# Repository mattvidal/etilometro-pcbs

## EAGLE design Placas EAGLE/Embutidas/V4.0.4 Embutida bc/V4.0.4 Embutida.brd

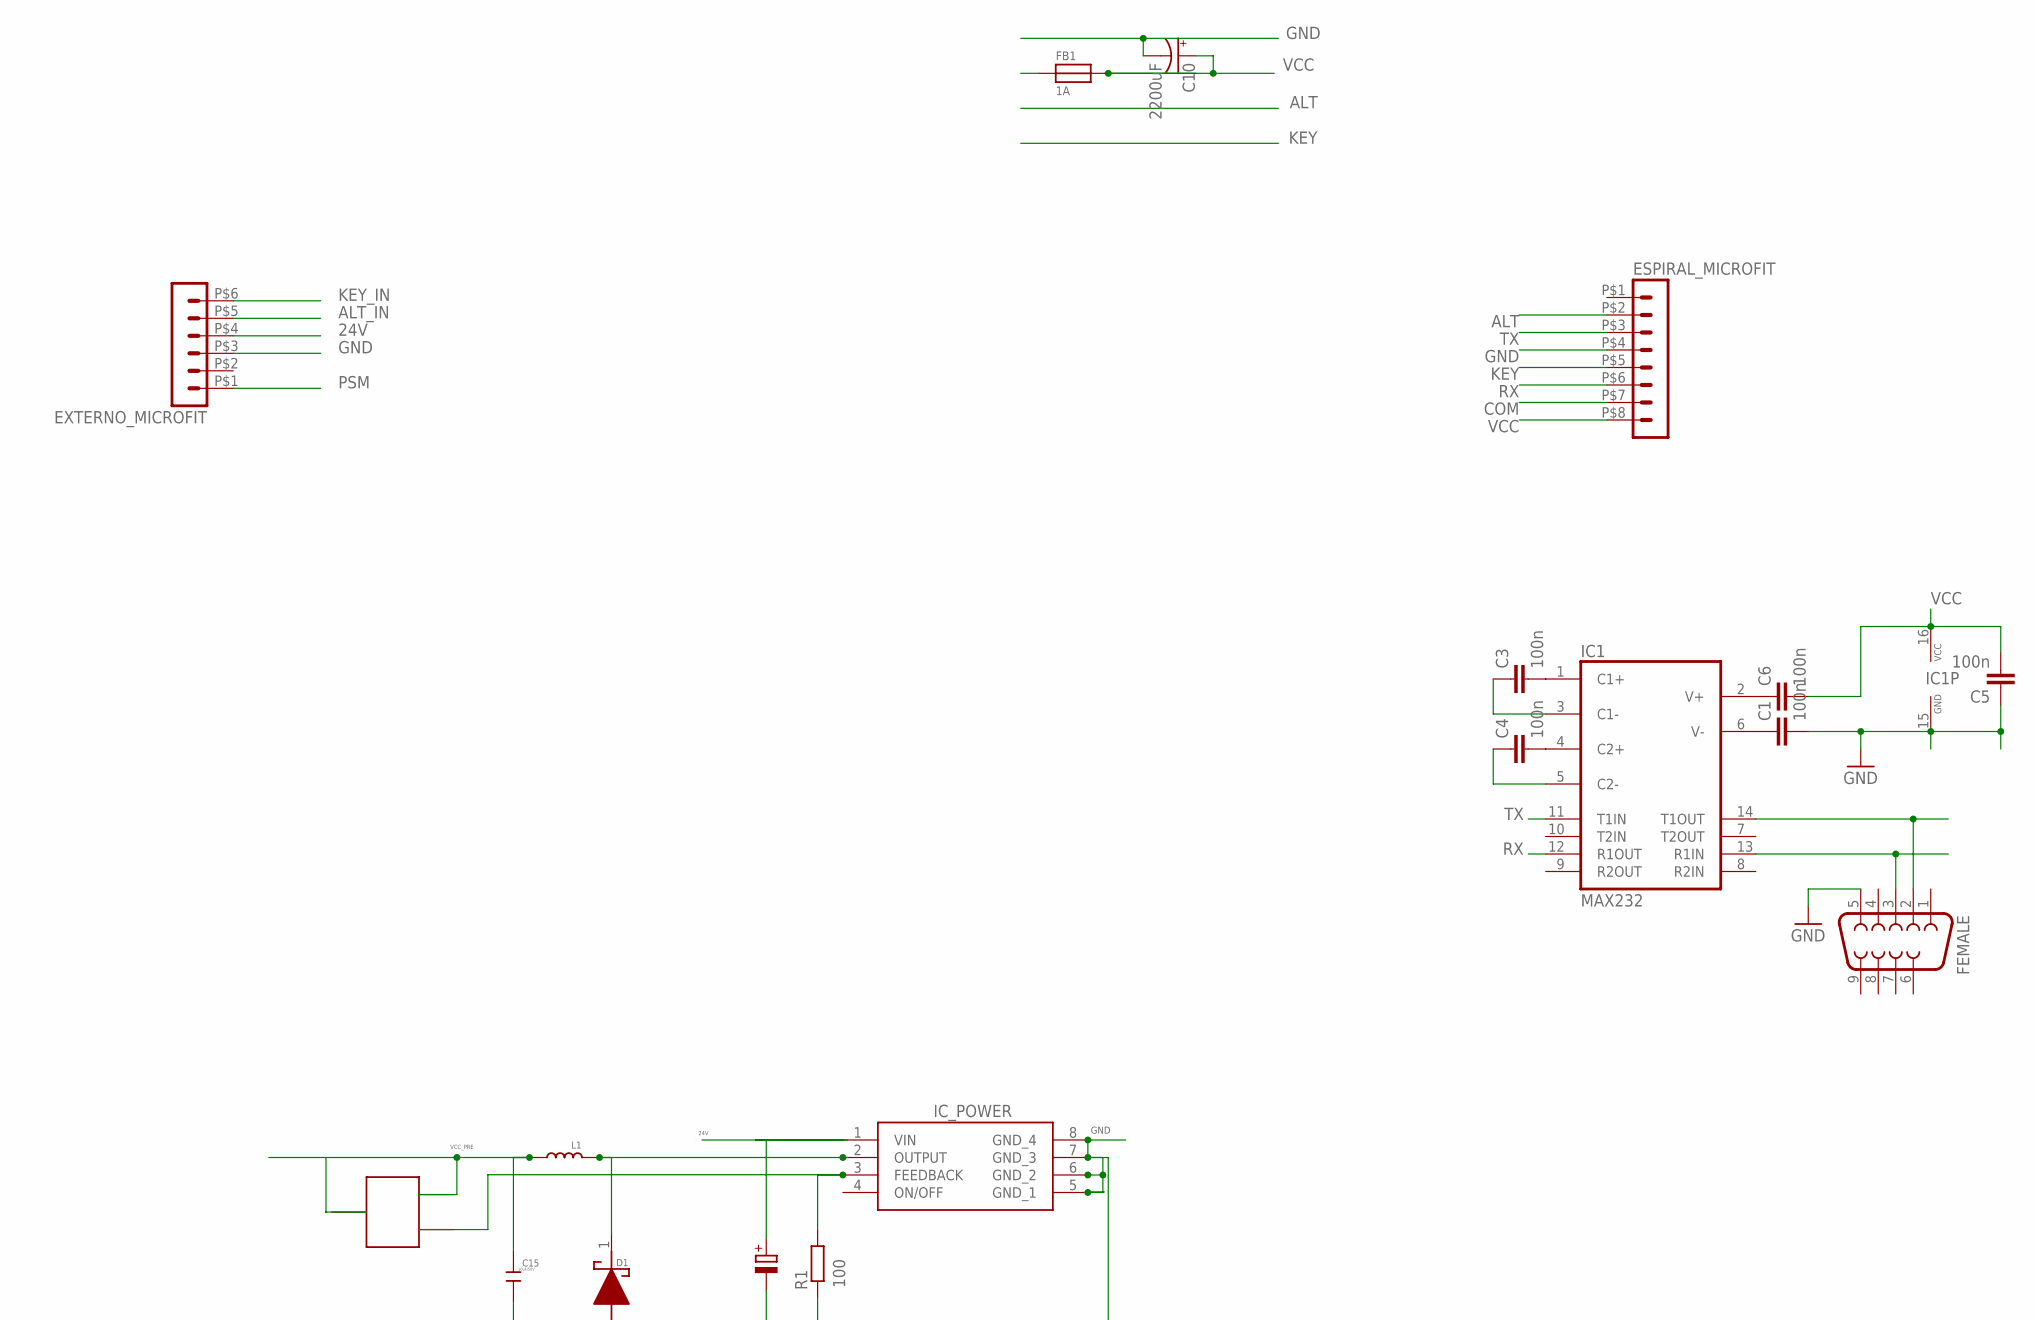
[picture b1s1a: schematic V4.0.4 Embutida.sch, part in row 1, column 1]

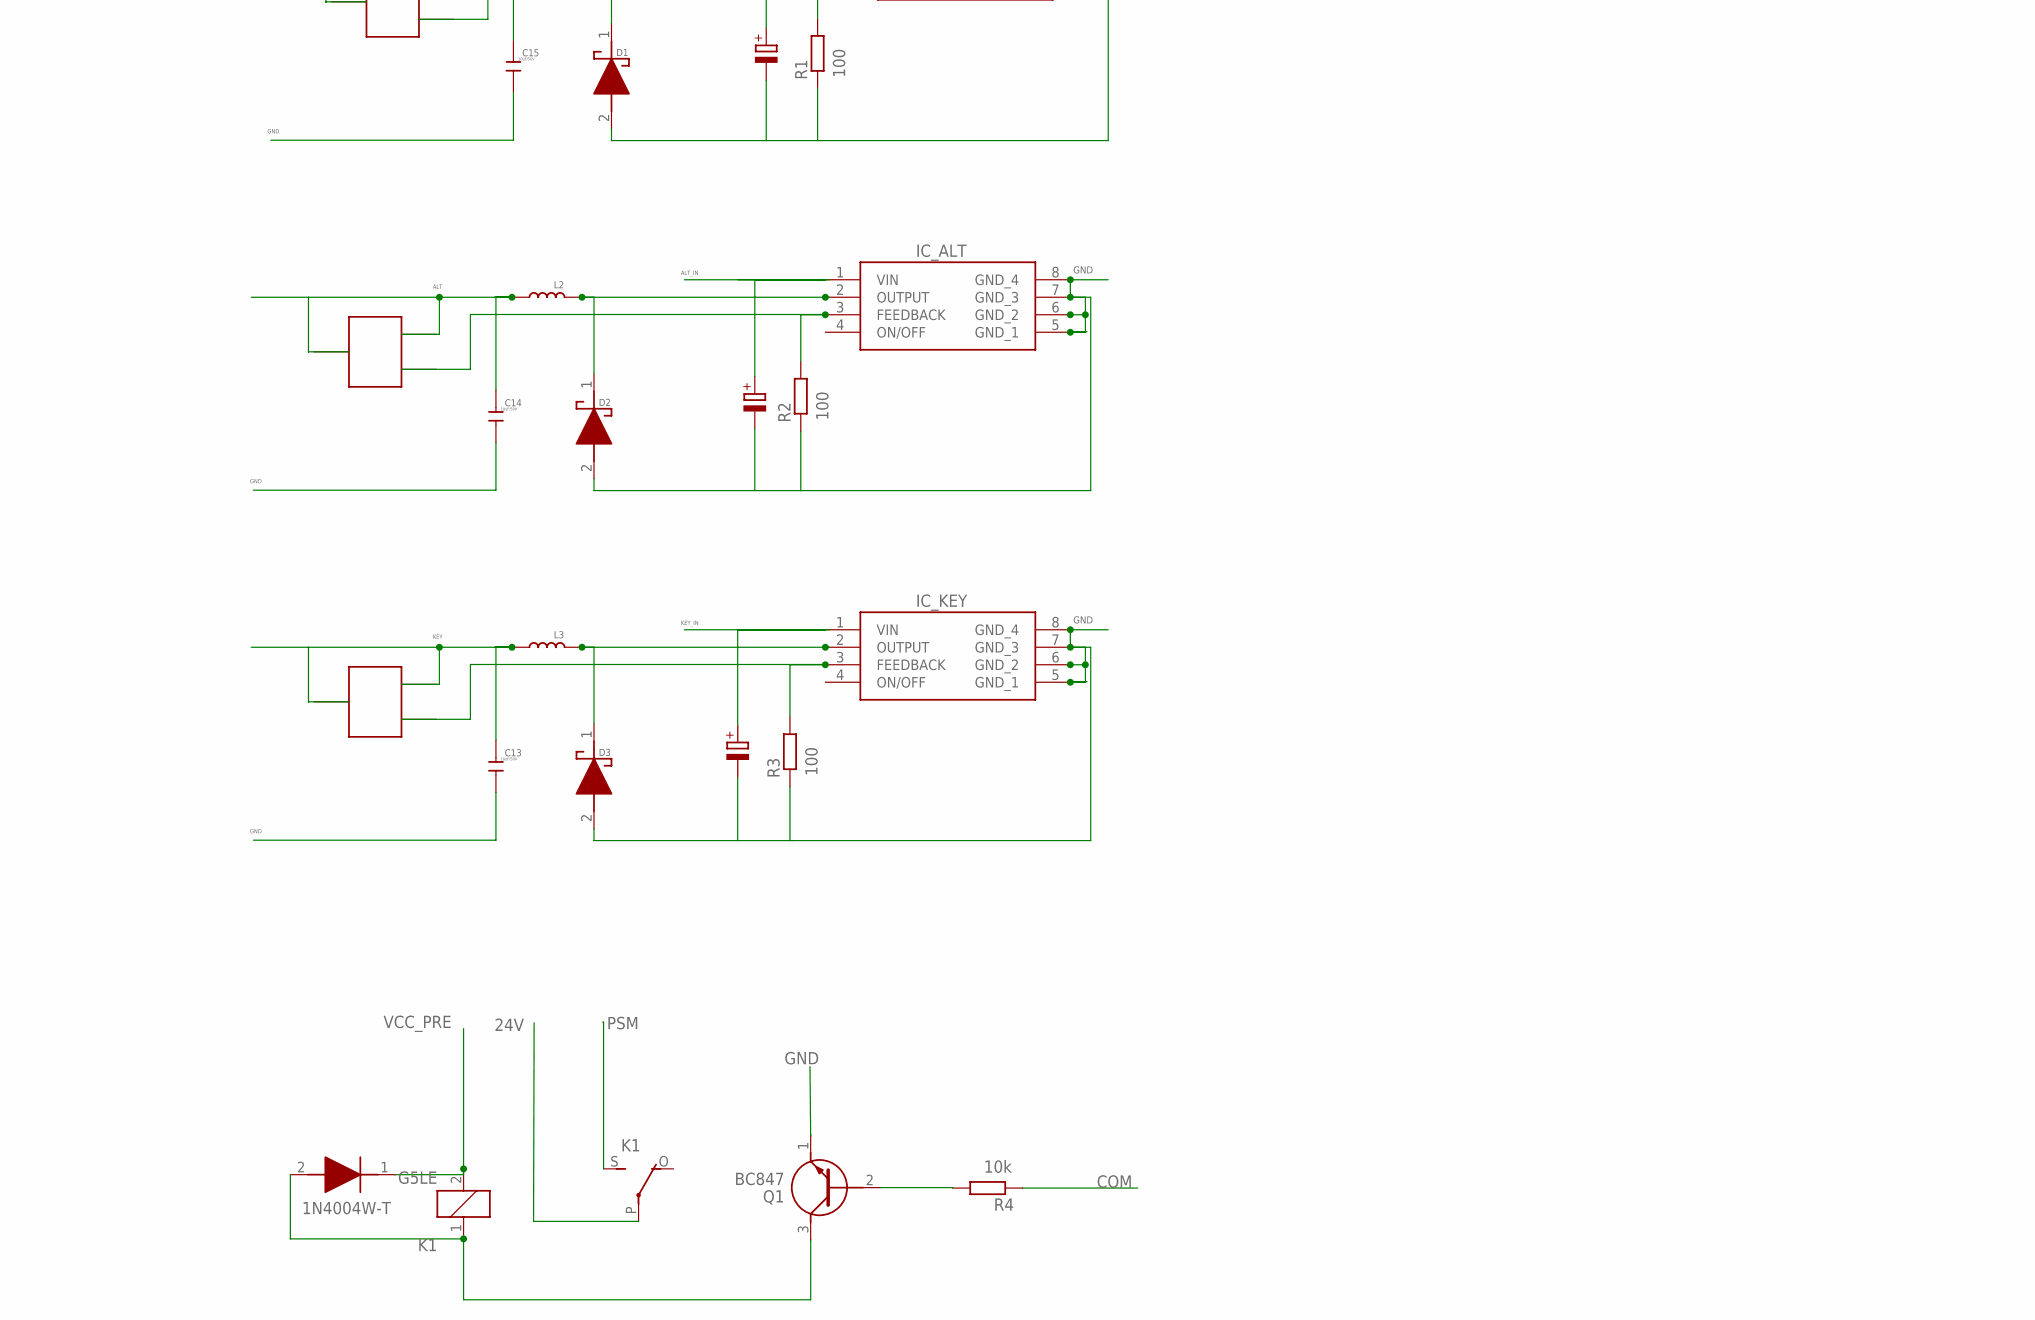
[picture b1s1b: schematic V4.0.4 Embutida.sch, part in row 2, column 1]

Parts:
C1, C3, C4, C5, C6: 100n; C0805; MPN C0805C104K8RACAUTO
C2: 22uF/50v; PANASONIC_D; MPN EEH-ZA1H220P
C8, C9: 22uF/50V; PANASONIC_D; MPN EEH-ZA1H220P
C10: 2200uF; PANASONIC_H13_MOD; MPN EEV-FK1A222Q
C13, C14, C15: 10uF/50V; C0805; MPN C2012X5R1H106K125AC
D1, D2, D3: 1N5819HW1-7-F; SODFL3518X115N; MPN 1N5822 SS34
D5: 1N4004W-T; SODFL3818X130N
ESPIRAL_MICROFIT: HEADER_POS8_43045-0800; 43045-0800; MPN 43045-0800
EXTERNO_MICROFIT: HEADER_POS6_43045-0600; 43045-0600; MPN 43045-0600
FB1: 1A; 0805; MPN BLM21AG121SN1D
FEMALE: F09H; MPN FEMALE DR9
IC1: MAX232; SO16; MPN MAX3232CSE+
IC_ALT: XL1509-3.3E1; SOIC127P600X175-8N; MPN XL1509-ADJE1
IC_KEY: XL1509-3.3E1; SOIC127P600X175-8N; MPN XL1509-ADJE1
IC_POWER: XL1509-3.3E1; SOIC127P600X175-8N; MPN XL1509-ADJE1
K1: G5LE
L1, L2, L3: 47uH; PIO73; MPN SDE0604A-470M
Q1: BC847
R1, R2, R3: 100; R0805; MPN RA73F2A100RBTDF
R4: 10k; R0805; MPN RA73F2A100RBTDF
T1, T2, T3: TRIMPOT 10K; TRIMPOT; MPN EVM3ESX50B14

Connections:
24V: C2.+, EXTERNO_MICROFIT.P$4 (4), IC_POWER.1 (VIN), K1.P
ALT: C14.2, ESPIRAL_MICROFIT.P$2 (2), L2.2, T2.VCC1, T2.VCC2
ALT_IN: C8.+, EXTERNO_MICROFIT.P$5 (5), IC_ALT.1 (VIN)
COM: ESPIRAL_MICROFIT.P$7 (7), R4.1
GND: C1.2, C2.-, C5.1, C8.-, C9.-, C10.-, C13.1, C14.1, C15.1, D1.2 (A), D2.2 (A), D3.2 (A), ESPIRAL_MICROFIT.P$4 (4), EXTERNO_MICROFIT.P$3 (3), FEMALE.5, IC1.15 (GND), IC_ALT.5 (GND_1), IC_ALT.6 (GND_2), IC_ALT.7 (GND_3), IC_ALT.8 (GND_4), IC_KEY.5 (GND_1), IC_KEY.6 (GND_2), IC_KEY.7 (GND_3), IC_KEY.8 (GND_4), IC_POWER.5 (GND_1), IC_POWER.6 (GND_2), IC_POWER.7 (GND_3), IC_POWER.8 (GND_4), Q1.1 (E), R1.1, R2.1, R3.1
KEY: C13.2, ESPIRAL_MICROFIT.P$5 (5), L3.2, T3.VCC1, T3.VCC2
KEY_IN: C9.+, EXTERNO_MICROFIT.P$6 (6), IC_KEY.1 (VIN)
unnamed: D1.1 (K), IC_POWER.2 (OUTPUT), L1.1
unnamed: D2.1 (K), IC_ALT.2 (OUTPUT), L2.1
unnamed: IC_ALT.3 (FEEDBACK), R2.2, T2.OUT
unnamed: D3.1 (K), IC_KEY.2 (OUTPUT), L3.1
unnamed: IC_KEY.3 (FEEDBACK), R3.2, T3.OUT
unnamed: D5.2 (A), K1.1, Q1.3 (C)
unnamed: IC_POWER.3 (FEEDBACK), R1.2, T1.OUT
unnamed: Q1.2 (B), R4.2
unnamed: C3.2, IC1.1 (C1+)
unnamed: C4.2, IC1.4 (C2+)
unnamed: C3.1, IC1.3 (C1-)
unnamed: C4.1, IC1.5 (C2-)
unnamed: C6.1, IC1.2 (V+)
unnamed: C1.1, IC1.6 (V-)
unnamed: FEMALE.2, IC1.14 (T1OUT)
unnamed: FEMALE.3, IC1.13 (R1IN)
PSM: EXTERNO_MICROFIT.P$1 (1), K1.S
RX: ESPIRAL_MICROFIT.P$6 (6), IC1.12 (R1OUT)
TX: ESPIRAL_MICROFIT.P$3 (3), IC1.11 (T1IN)
VCC: C5.2, C6.2, C10.+, ESPIRAL_MICROFIT.P$8 (8), FB1.2, IC1.16 (VCC)
VCC_PRE: C15.2, D5.1 (K), FB1.1, K1.2, L1.2, T1.VCC1, T1.VCC2

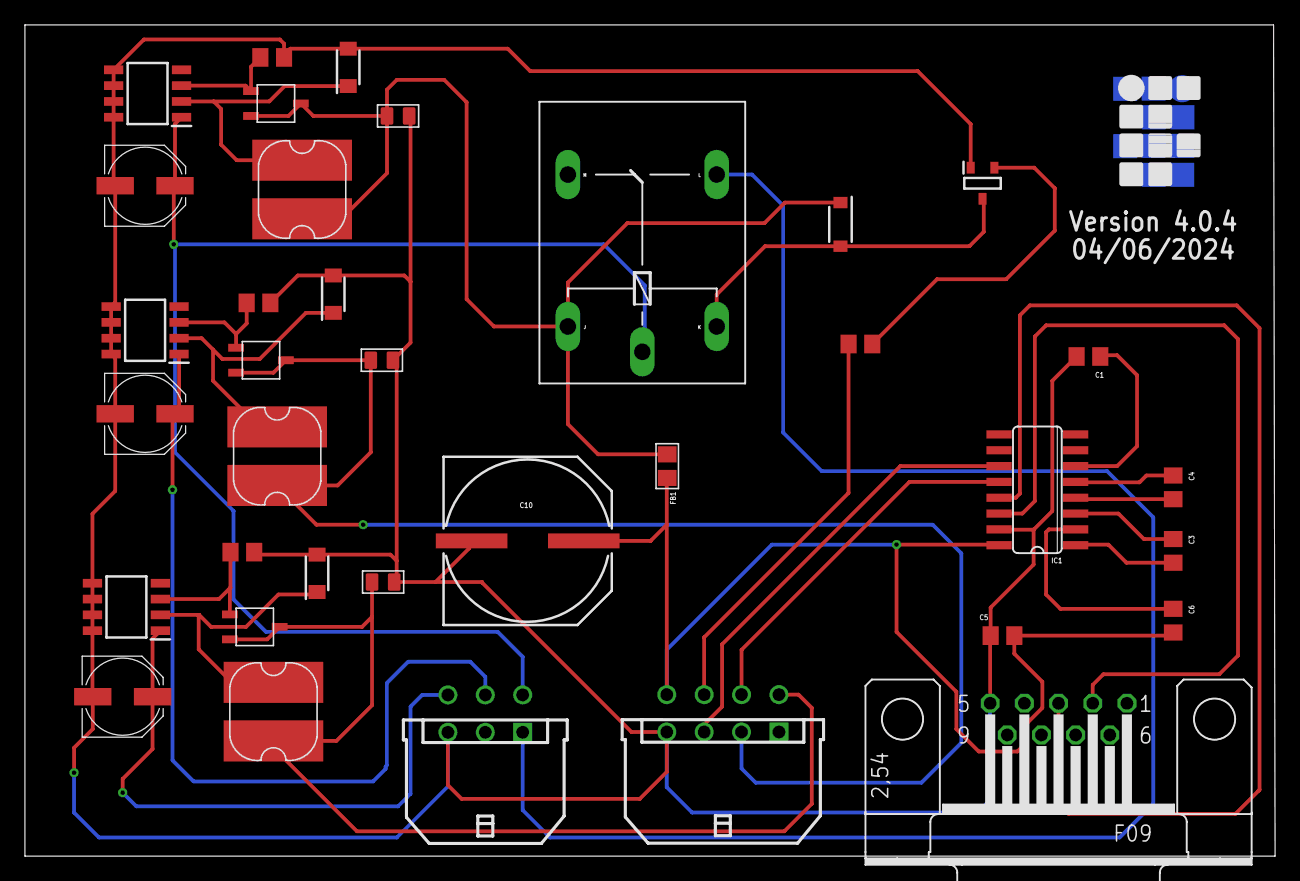
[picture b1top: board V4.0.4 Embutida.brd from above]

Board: 2 copper layers, 100.3 x 66.7 mm, 36 parts (0 on the bottom side), 28 nets.

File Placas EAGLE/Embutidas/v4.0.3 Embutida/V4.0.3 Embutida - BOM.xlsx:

Part | Value | MPN
C1 | 100n | C0805C104K8RACAUTO
C2 | 22uF/50v | EEH-ZA1H220P
C3 | 100n | C0805C104K8RACAUTO
C4 | 100n | C0805C104K8RACAUTO
C5 | 100n | C0805C104K8RACAUTO
C6 | 100n | C0805C104K8RACAUTO
C8 | 22uF/50V | EEH-ZA1H220P
C9 | 22uF/50V | EEH-ZA1H220P
C10 | 2200 uF | EEV-FK1A222Q
C13 | 10uF/50V | C2012X5R1H106K125AC
C14 | 10uF/50V | C2012X5R1H106K125AC
C15 | 10uF/50V | C2012X5R1H106K125AC
D1 | 1N5819HW1-7-F | 1N5822 SS34
D2 | 1N5819HW1-7-F | 1N5822 SS34
D3 | 1N5819HW1-7-F | 1N5822 SS34
D5 |  | 1N4004W-T
ESPIRAL_MICROFIT |  | 43045-0800
EXTERNO_MICROFIT |  | 43045-0600
FB1 | 1A | BLM21AG121SN1D
FEMALE |  | FEMALE DR9
IC1 | MAX232 | MAX3232CSE+
IC_ALT | XL1509-3.3E1 | XL1509-ADJE1
IC_KEY | XL1509-3.3E1 | XL1509-ADJE1
IC_POWER | XL1509-3.3E1 | XL1509-ADJE1
K1 |  | G5LE
L1 | 47uH | SDE0604A-470M
L2 | 47uH | SDE0604A-470M
L3 | 47uH | SDE0604A-470M
Q1 |  | BC847
R1 | 100 | RA73F2A100RBTDF
R2 | 100 | RA73F2A100RBTDF
R3 | 100 | RA73F2A100RBTDF
R4 | 10k | RA73F2A100RBTDF
T1 | TRIMPOT 10K | EVM3ESX50B14
T2 | TRIMPOT 10K | EVM3ESX50B14
T3 | TRIMPOT 10K | EVM3ESX50B14

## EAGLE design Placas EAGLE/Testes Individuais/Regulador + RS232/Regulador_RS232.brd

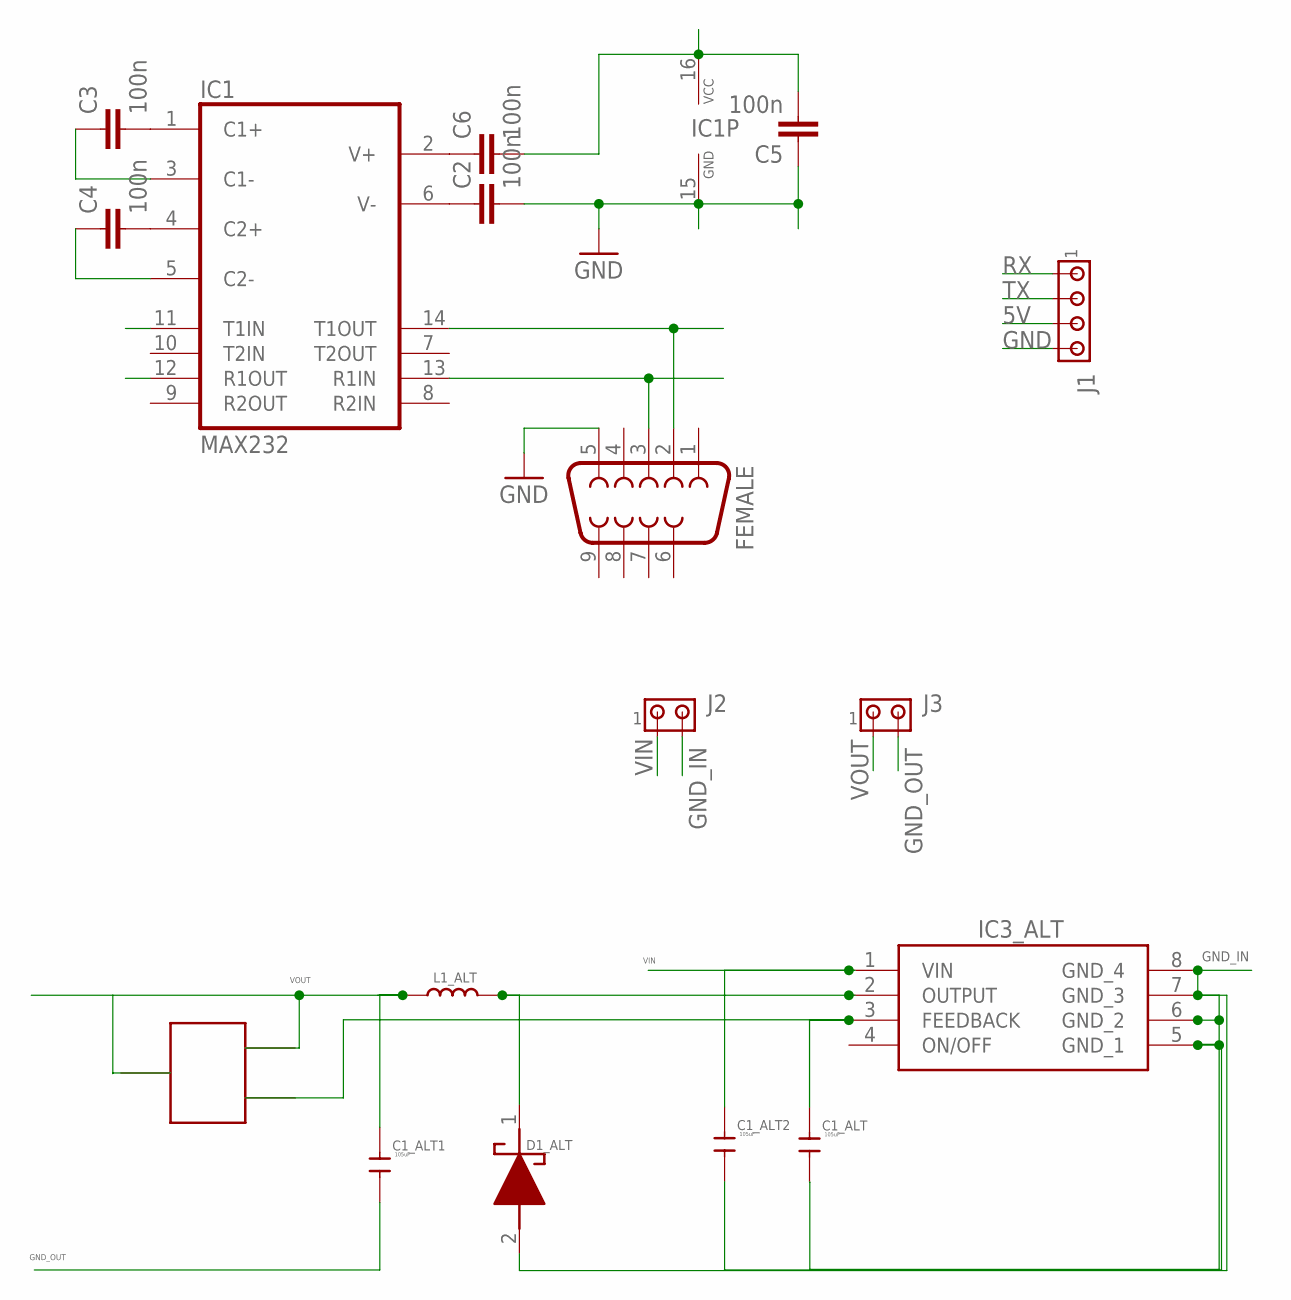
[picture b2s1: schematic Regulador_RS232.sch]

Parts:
C1_ALT, C1_ALT1, C1_ALT2: 105uF; C0805
C2, C3, C4, C5, C6: 100n; C0805
D1_ALT: 1N5819HW1-7-F; SODFL3518X115N
FEMALE: F09H
IC1: MAX232; SO16
IC3_ALT: XL1509-3.3E1; SOIC127P600X175-8N
J1: MTA04-156; 1X4MTA
J2, J3: MTA02-156; 1X2MTA
L1_ALT: 47uH; PIO73
U$1: TRIMPOT

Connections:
5V: C5.2, C6.2, IC1.16 (VCC), J1.3
GND: C2.2, C5.1, FEMALE.5, IC1.15 (GND), J1.4
GND_IN: C1_ALT.1, C1_ALT2.1, D1_ALT.2 (A), IC3_ALT.5 (GND_1), IC3_ALT.6 (GND_2), IC3_ALT.7 (GND_3), IC3_ALT.8 (GND_4), J2.2
GND_OUT: C1_ALT1.1, J3.2
unnamed: D1_ALT.1 (K), IC3_ALT.2 (OUTPUT), L1_ALT.1
unnamed: C1_ALT.2, IC3_ALT.3 (FEEDBACK), U$1.OUT
unnamed: C3.2, IC1.1 (C1+)
unnamed: C4.2, IC1.4 (C2+)
unnamed: C3.1, IC1.3 (C1-)
unnamed: C4.1, IC1.5 (C2-)
unnamed: C6.1, IC1.2 (V+)
unnamed: C2.1, IC1.6 (V-)
unnamed: FEMALE.2, IC1.14 (T1OUT)
unnamed: FEMALE.3, IC1.13 (R1IN)
RX: IC1.12 (R1OUT), J1.1
TX: IC1.11 (T1IN), J1.2
VIN: C1_ALT2.2, IC3_ALT.1 (VIN), J2.1
VOUT: C1_ALT1.2, J3.1, L1_ALT.2, U$1.VCC1, U$1.VCC2

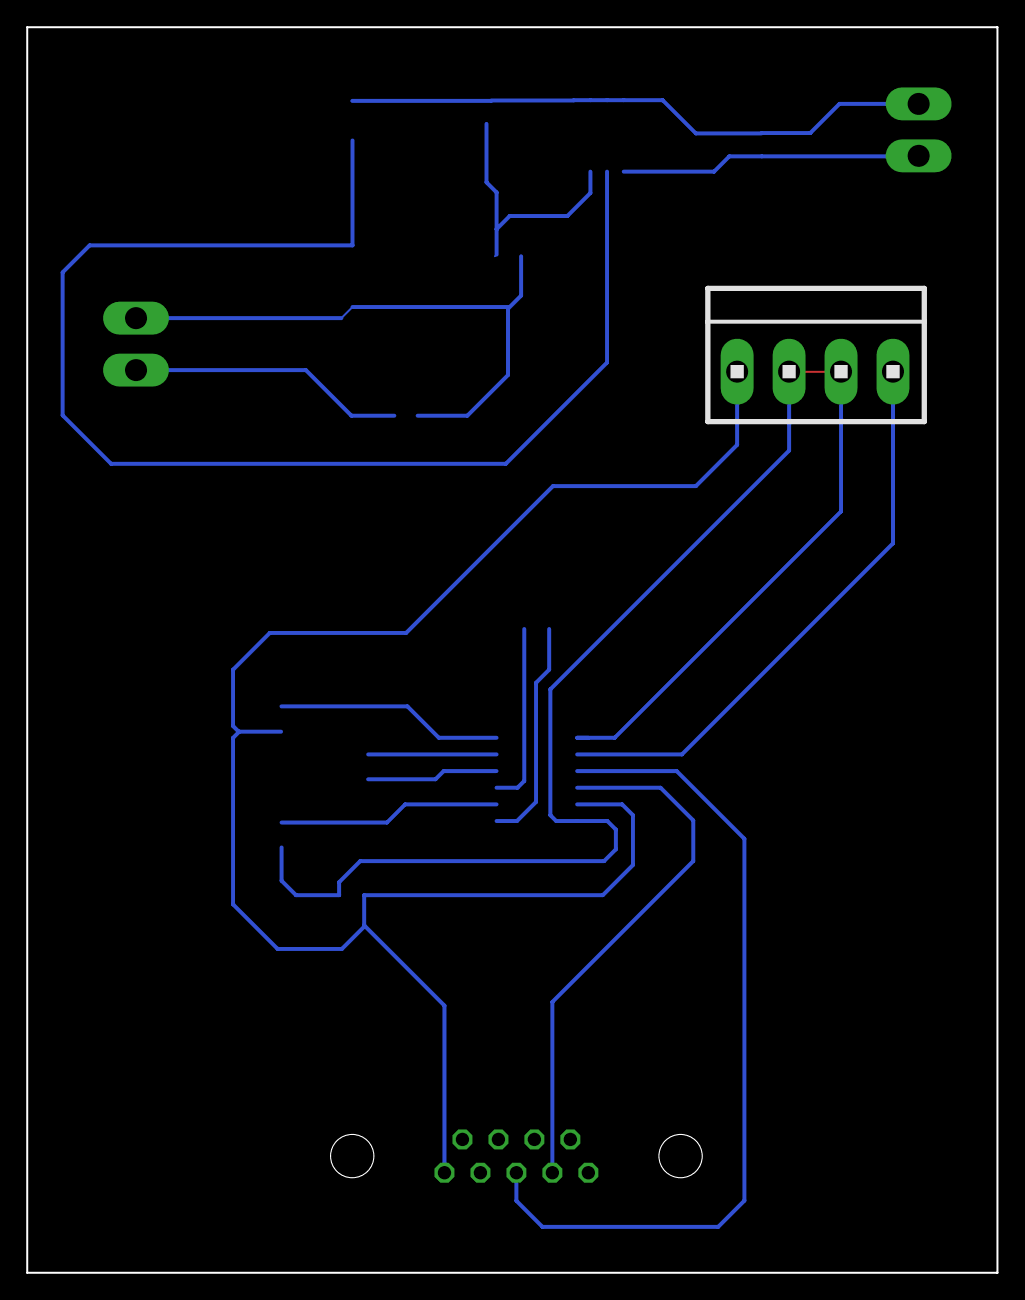
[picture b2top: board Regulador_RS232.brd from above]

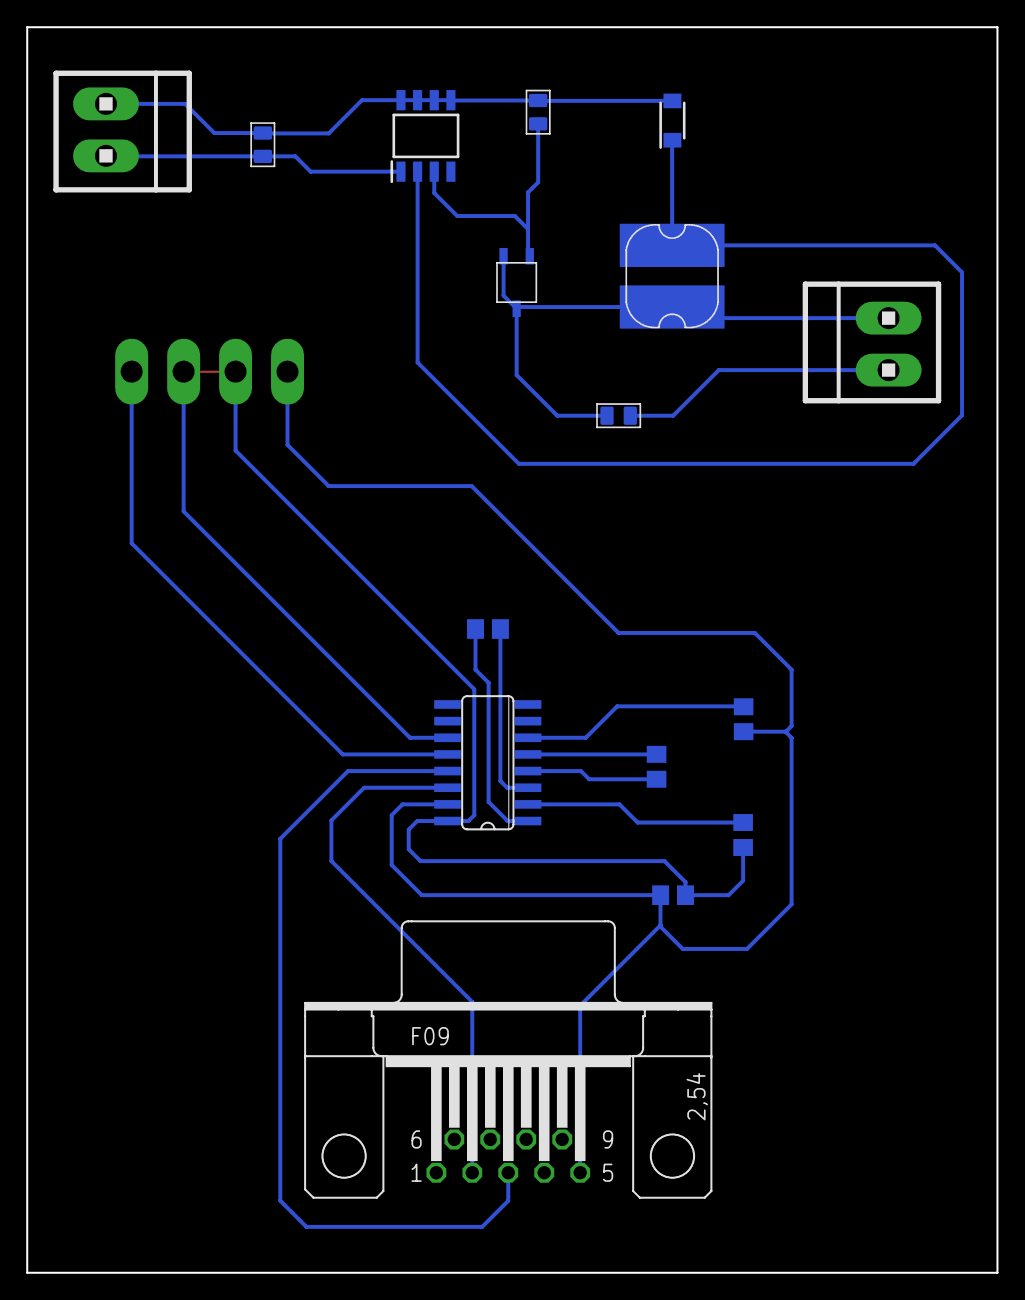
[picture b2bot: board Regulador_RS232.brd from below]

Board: 2 copper layers, 74.0 x 95.0 mm, 17 parts (16 on the bottom side), 18 nets.

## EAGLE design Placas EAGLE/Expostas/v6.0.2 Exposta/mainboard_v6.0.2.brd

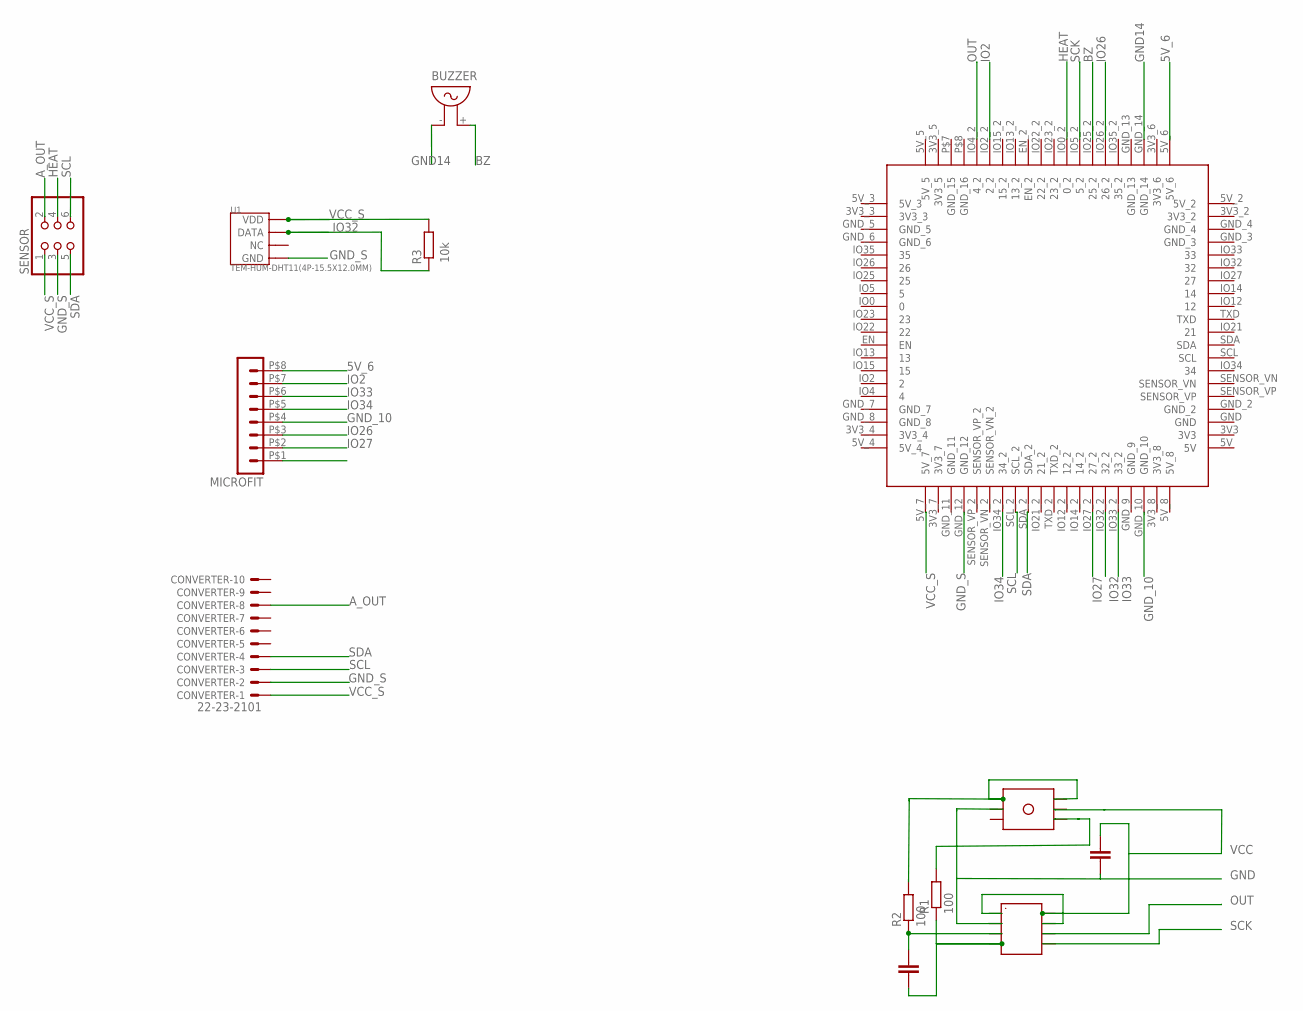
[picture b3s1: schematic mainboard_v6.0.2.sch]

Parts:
BUZZER: F/QMX
C1, C2: 100n; C0805
CONVERTER: 22-23-2101
MICROFIT: HEADER_POS8_43045-0800; 43045-0800
R1, R2: 100; R0805
R3: 10k; R0805
SENSOR: PINHD-2X3; 2X03
U1: TEM-HUM-DHT11(4P-15.5X12.0MM); SNR4-2.54-15.5X12.0X5.5MM
U$1: WT32_SC01WT32_D; WT32_DUPLICATED
U$2: HX710B; HX710B_SMD
U$3: PRESSUREPRESSURE_PTH; PRESSURE_PTH

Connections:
5V_6: MICROFIT.P$8 (8), U$1.5V_6
A_OUT: CONVERTER.8, SENSOR.2
BZ: BUZZER.+ (2), U$1.IO25_2 (25_2)
GND: C2.2, U$2.AGND, U$3.2
GND14: BUZZER.- (1), U$1.GND_14
GND_10: MICROFIT.P$4 (4), U$1.GND_10
GND_S: CONVERTER.2, SENSOR.3, U1.4 (GND), U$1.GND_12
HEAT: SENSOR.4, U$1.IO0_2 (0_2)
IO2: MICROFIT.P$7 (7), U$1.IO2_2 (2_2)
IO26: MICROFIT.P$3 (3), U$1.IO26_2 (26_2)
IO27: MICROFIT.P$2 (2), U$1.IO27_2 (27_2)
IO32: R3.1, U1.2 (DATA), U$1.IO32_2 (32_2)
IO33: MICROFIT.P$6 (6), U$1.IO33_2 (33_2)
IO34: MICROFIT.P$5 (5), U$1.IO34_2 (34_2)
unnamed: C1.2, R2.1, U$2.INN
unnamed: C1.1, R1.1, U$2.INP
unnamed: R1.2, U$3.4
unnamed: R2.2, U$3.1, U$3.6
OUT: U$1.IO4_2 (4_2), U$2.DOUT
SCK: U$1.IO5_2 (5_2), U$2.SCK
SCL: CONVERTER.3, SENSOR.6, U$1.SCL_2
SDA: CONVERTER.4, SENSOR.5, U$1.SDA_2
VCC: C2.1, U$2.AVDD, U$2.DVDD, U$2.VREF, U$3.5
VCC_S: CONVERTER.1, R3.2, SENSOR.1, U1.1 (VDD), U$1.5V_7

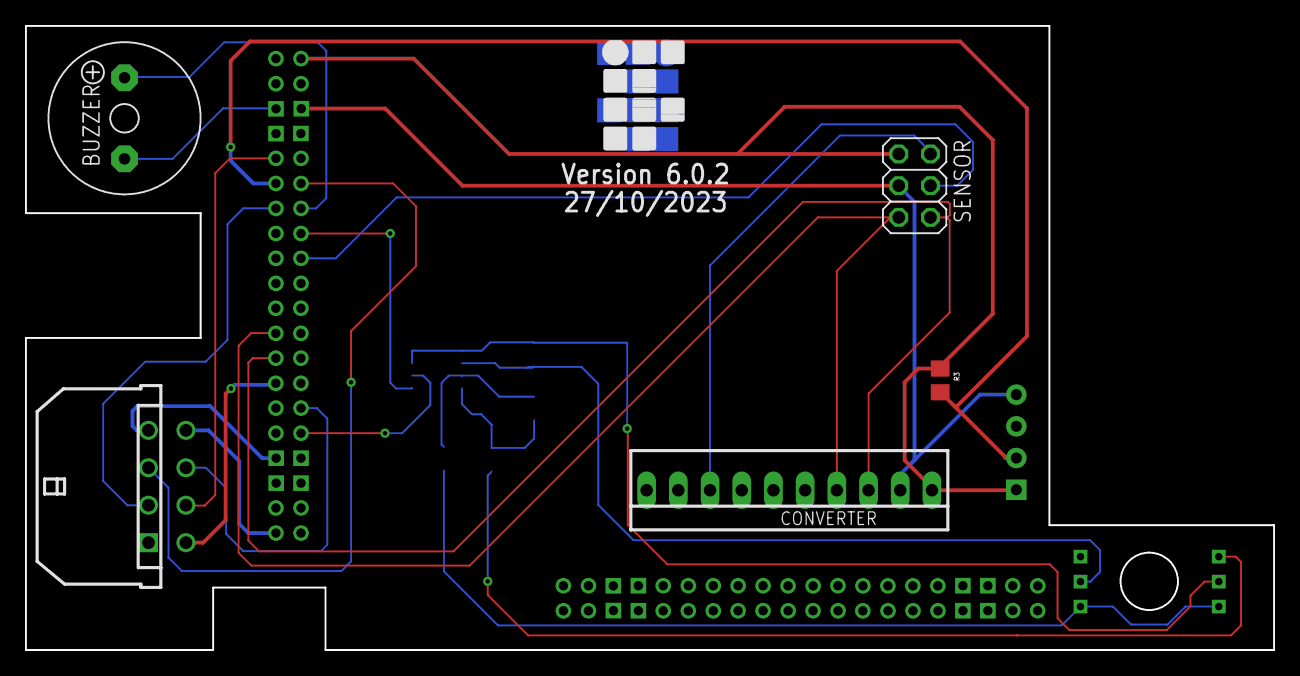
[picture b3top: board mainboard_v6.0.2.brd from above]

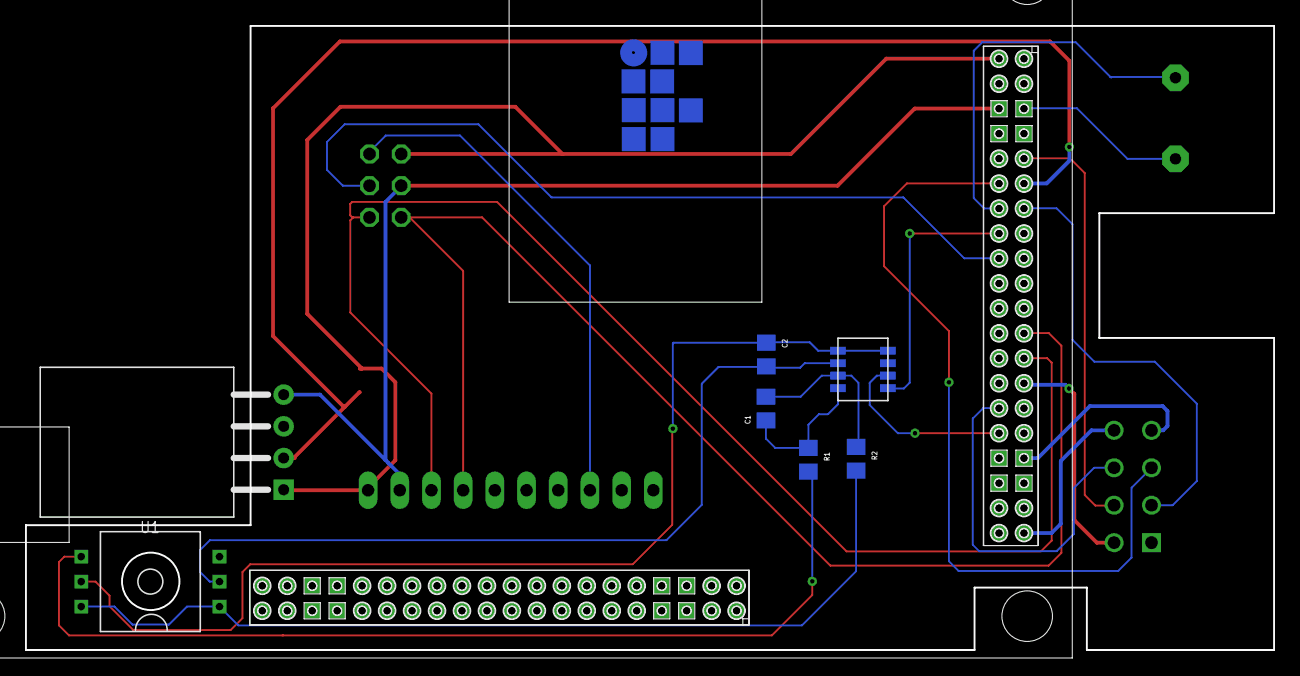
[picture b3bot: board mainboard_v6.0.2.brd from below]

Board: 2 copper layers, 100.0 x 50.0 mm, 13 parts (8 on the bottom side), 24 nets.

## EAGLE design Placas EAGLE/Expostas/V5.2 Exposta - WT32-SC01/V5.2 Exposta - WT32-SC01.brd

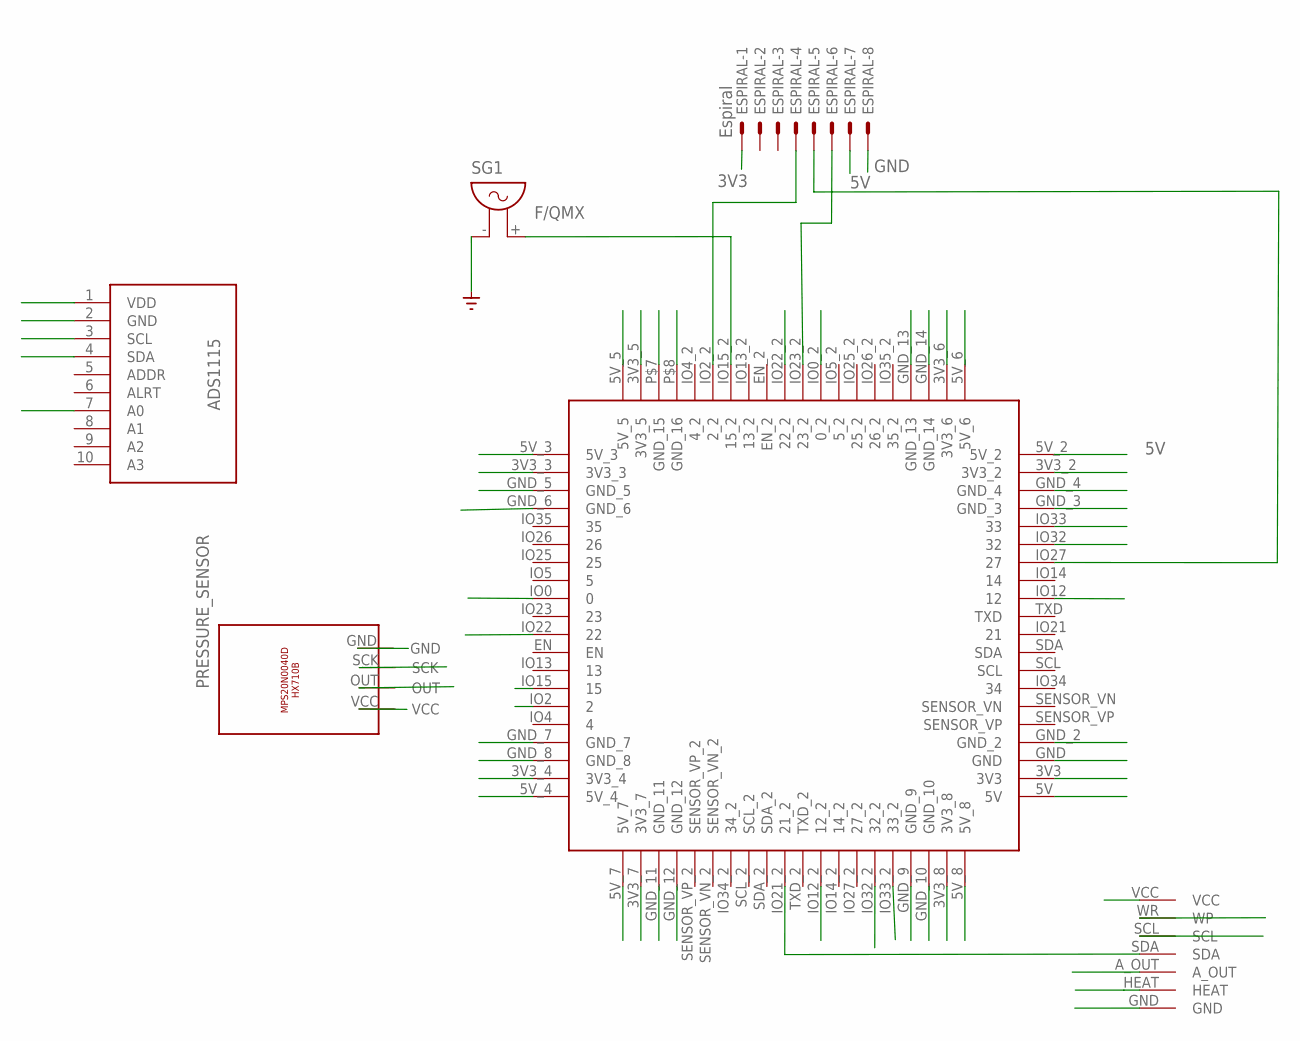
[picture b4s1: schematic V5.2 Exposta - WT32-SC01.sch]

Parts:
ESPIRAL: Espiral; 7395-08
PRESSURE_SENSOR: PRESSURE_SENSORWITH_SMDPADS&THROUGHHOLES; MPS20N0040D
SG1: F/QMX
U$1: SENSOR
U$2: WT32_SC01; WT32
U$3: ADS1115

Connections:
3V3: ESPIRAL.1, U$2.3V3, U$2.3V3_2, U$2.3V3_3, U$2.3V3_4, U$2.3V3_5, U$2.3V3_6
5V: ESPIRAL.7, PRESSURE_SENSOR.VCC, U$1.VCC, U$2.5V, U$2.5V_2, U$2.5V_3, U$2.5V_4, U$2.5V_5, U$2.5V_6, U$2.5V_7, U$2.5V_8, U$3.1 (VDD)
A_OUT: U$1.A_OUT, U$3.7 (A0)
GND: ESPIRAL.8, PRESSURE_SENSOR.GND, SG1.- (1), U$1.GND, U$2.GND, U$2.GND_2, U$2.GND_3, U$2.GND_4, U$2.GND_5, U$2.GND_6, U$2.GND_7, U$2.GND_8, U$2.GND_9, U$2.GND_10, U$2.GND_11, U$2.GND_12, U$2.GND_13, U$2.GND_14, U$2.P$7 (GND_15), U$2.P$8 (GND_16), U$3.2 (GND)
IO0: U$1.HEAT, U$2.IO0 (0), U$2.IO0_2 (0_2)
IO2: ESPIRAL.4, U$2.IO2 (2), U$2.IO2_2 (2_2)
IO12: U$1.WR (WP), U$2.IO12 (12), U$2.IO12_2 (12_2)
IO15: SG1.+ (2), U$2.IO15 (15), U$2.IO15_2 (15_2)
IO21: U$1.SDA, U$2.IO21_2 (21_2), U$3.4 (SDA)
IO22: U$1.SCL, U$2.IO22 (22), U$2.IO22_2 (22_2), U$3.3 (SCL)
IO32: PRESSURE_SENSOR.OUT, U$2.IO32 (32), U$2.IO32_2 (32_2)
IO33: PRESSURE_SENSOR.SCK, U$2.IO33 (33), U$2.IO33_2 (33_2)
unnamed: ESPIRAL.6, U$2.IO23_2 (23_2)
unnamed: ESPIRAL.5, U$2.IO27 (27)

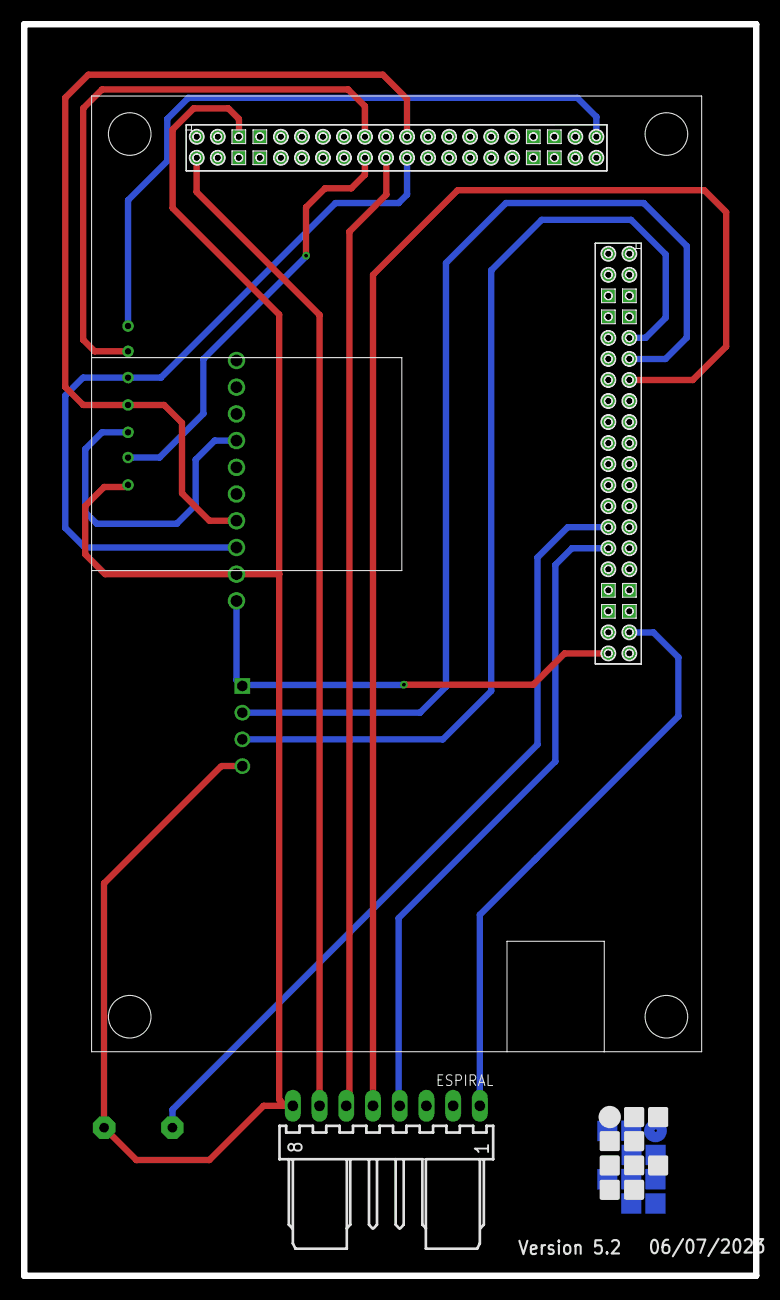
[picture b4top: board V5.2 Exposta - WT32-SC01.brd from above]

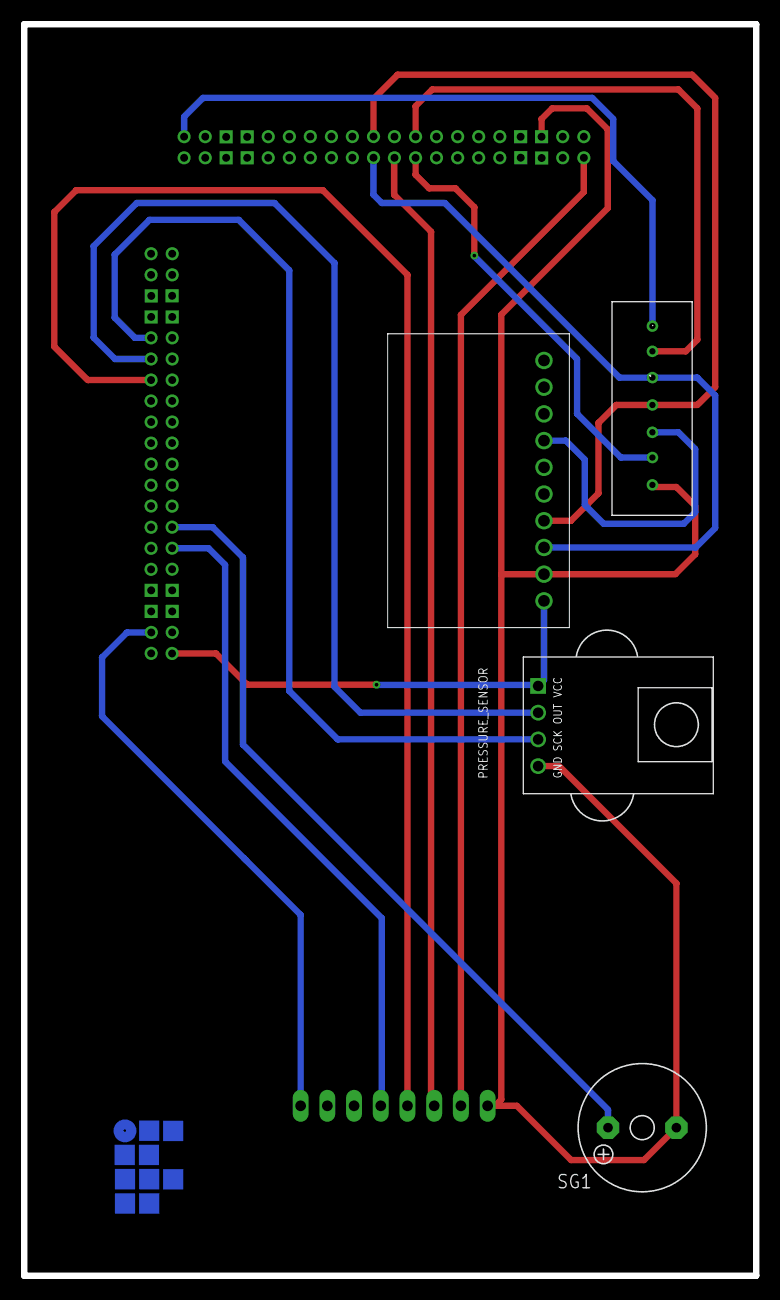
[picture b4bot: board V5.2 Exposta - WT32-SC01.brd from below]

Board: 2 copper layers, 69.6 x 119.0 mm, 6 parts (4 on the bottom side), 14 nets.

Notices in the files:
parts and their libraries:
SparkFun-Fuses: Licensing: Creative Commons ShareAlike 4.0 International - https://creativecommons.org/licenses/by-sa/4.0
SparkFun-Capacitors: Licensing: CC v3.0 Share-Alike You are welcome to use this library for commercial purposes.
